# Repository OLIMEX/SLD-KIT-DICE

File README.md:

# SLD-KIT-DICE

Electronic dice soldering kit: shake it, and it spins with sound and lands on a random number.

- CH32V003J4M6 RISC-V microcontroller, 7 LEDs, shock sensor, speaker
- One CR2032 coin cell, ~6 µA in standby
- Through-hole parts only, except the SOP-8 microcontroller

Български: [README_BG.md](README_BG.md)

## Licensee
* Hardware is released under CERN Open Hardware Licence Version 2 - Strongly Reciprocal https://spdx.org/licenses/CERN-OHL-S-2.0.html
* Software is released under MIT Licensee
* Documentation is released under CC BY-SA 4.0 https://creativecommons.org/licenses/by-sa/4.0/

## Repository

| Folder | Content |
|---|---|
| [DOCUMENTS](DOCUMENTS) | [Soldering guide](DOCUMENTS/SLD-KIT-DICE_Soldering_Guide.pdf) and 2-page quick guide in [English](DOCUMENTS/SLD-KIT-DICE_Quick_Soldering_Guide.pdf) and [Bulgarian](DOCUMENTS/SLD-KIT-DICE_Quick_Soldering_Guide_BG.pdf) (PDF, and ODT to edit) |
| [HARDWARE/SLD-KIT-DICE_Rev_A](HARDWARE/SLD-KIT-DICE_Rev_A) | KiCad project, [schematic (PDF)](HARDWARE/SLD-KIT-DICE_Rev_A/SLD-KIT-DICE_Rev_A.pdf), [BOM](HARDWARE/SLD-KIT-DICE_Rev_A/SLD-KIT-DICE_Rev_A_BOM.csv), Gerber files, 3D models |
| [SOFTWARE/SLD-KIT-DICE_FW](SOFTWARE/SLD-KIT-DICE_FW) | Firmware source (ch32fun + PlatformIO) |
| [SOFTWARE/SLD-KIT-DICE_FW/firmware](SOFTWARE/SLD-KIT-DICE_FW/firmware) | Ready-to-flash images |

## Programming

Connect a WCH-LinkE to the PGM/DBG header: pin 1 = SWIO, pin 2 = GND. The header has no VCC, so the battery must be in. The chip accepts the programmer only in the first 3 s after the battery is put in: start the command, then put the battery in.

```bash
cd SOFTWARE/SLD-KIT-DICE_FW
until minichlink -w firmware/dice.bin 0x08000000 -b; do sleep 0.2; done
```

With PlatformIO (builds and flashes):

```bash
cd SOFTWARE/SLD-KIT-DICE_FW
until pio run -t upload; do sleep 0.2; done
```

How the firmware works, how to build it and how to debug it: [SOFTWARE/SLD-KIT-DICE_FW/README.md](SOFTWARE/SLD-KIT-DICE_FW/README.md).

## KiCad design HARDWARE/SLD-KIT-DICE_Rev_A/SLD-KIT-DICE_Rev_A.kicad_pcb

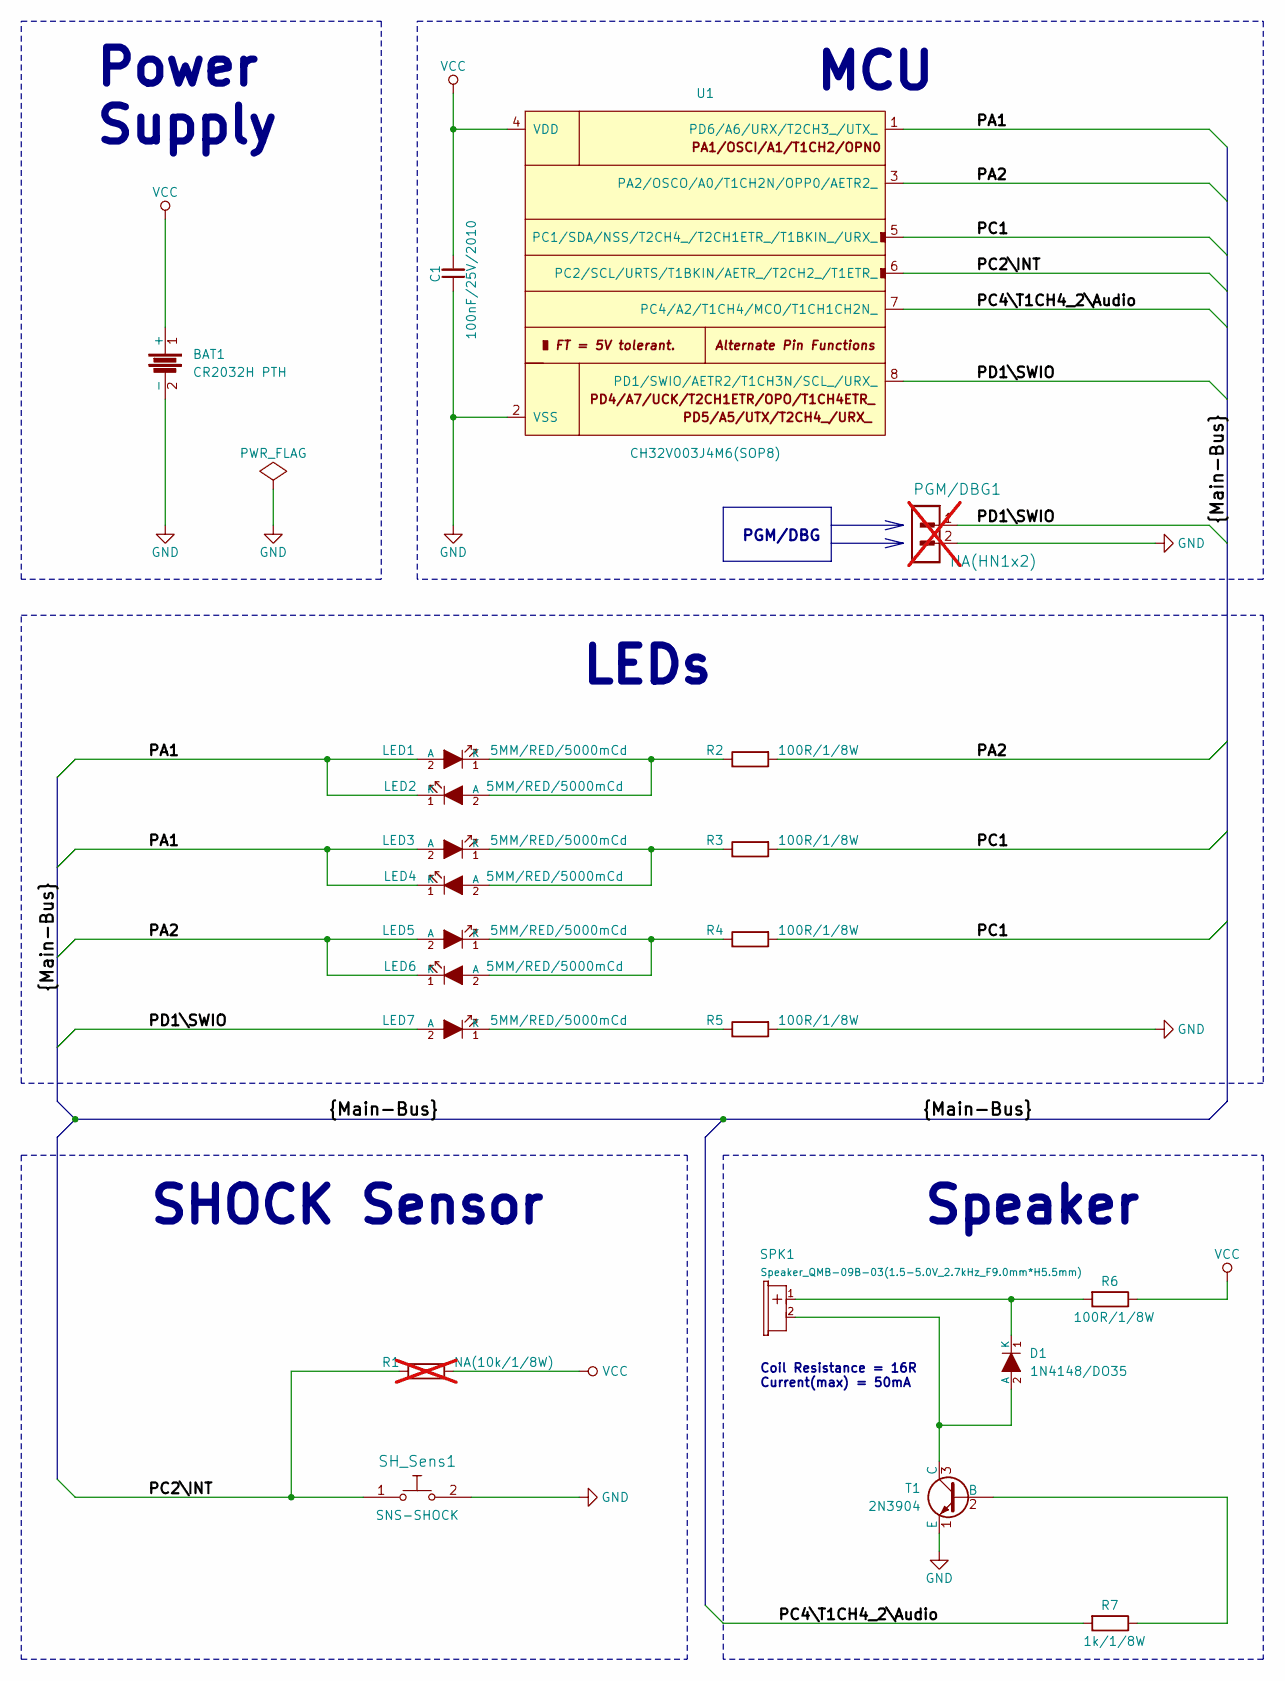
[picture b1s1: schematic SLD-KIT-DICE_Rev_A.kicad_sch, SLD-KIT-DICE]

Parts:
BAT1: CR2032H PTH; CR2032H_PTH
C1: 100nF/25V/2010; C2010
D1: 1N4148/DO35; DO35_1K_2A
LED1, LED2, LED3, LED4, LED5, LED6, LED7: 5MM/RED/5000mCd; LED-5mm-PTH-KA
PGM/DBG1: NA(HN1x2); HN1x2; not fitted
R1: NA(10k/1/8W); R_0.125W_PTH; not fitted
R2, R3, R4, R5, R6: 100R/1/8W; R_0.125W_PTH
R7: 1k/1/8W; R_0.125W_PTH
SH_Sens1: SNS-SHOCK; SNS-SHOCK-SENSOR
SPK1: Speaker_QMB-09B-03(1.5-5.0V_2.7kHz_F9.0mm*H5.5mm); Speaker_QMB-09B-03_1-Plus_2-Minus
T1: 2N3904; TO-92_PTH
U1: CH32V003J4M6(SOP8); SOIC-8_150mil

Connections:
/PA1: LED1.2 (A), LED2.1 (K), LED3.2 (A), LED4.1 (K), U1.1 (PD6/A6/URX/T2CH3_/UTX_)
/PA2: LED5.2 (A), LED6.1 (K), R2.2, U1.3 (PA2/OSCO/A0/T1CH2N/OPP0/AETR2_)
/PC1: R3.2, R4.2, U1.5 (PC1/SDA/NSS/T2CH4_/T2CH1ETR_/T1BKIN_/UR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)
/PC2\INT: R1.1, SH_Sens1.1, U1.6 (PC2/SCL/URTS/T1BKIN/AETR_/T2CH2_/T1ETR_)
/PC4\T1CH4_2\Audio: R7.2, U1.7 (PC4/A2/T1CH4/MCO/T1CH1CH2N_)
/PD1\SWIO: LED7.2 (A), PGM/DBG1.1, U1.8 (PD1/SWIO/AETR2/T1CH3N/SCL_/URX_)
GND: BAT1.2 (-), C1.1, PGM/DBG1.2, R5.2, SH_Sens1.2, T1.1 (E), U1.2 (VSS)
unnamed: D1.2 (A), SPK1.2 (MINUS), T1.3 (C)
unnamed: D1.1 (K), R6.2, SPK1.1 (PLUS)
unnamed: LED1.1 (K), LED2.2 (A), R2.1
unnamed: LED3.1 (K), LED4.2 (A), R3.1
unnamed: LED5.1 (K), LED6.2 (A), R4.1
unnamed: LED7.1 (K), R5.1
unnamed: R7.1, T1.2 (B)
VCC: BAT1.1 (+), C1.2, R1.2, R6.1, U1.4 (VDD)

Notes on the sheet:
Power Supply
LEDs
MCU
Speaker
Coil Resistance = 16R Current(max) = 50mA
PGM/DBG
SHOCK Sensor

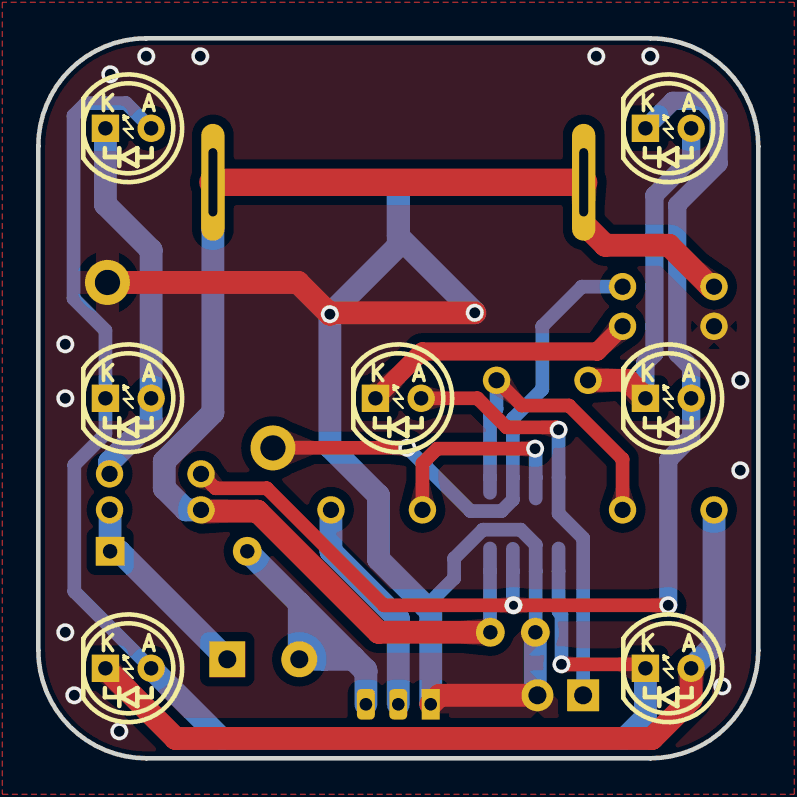
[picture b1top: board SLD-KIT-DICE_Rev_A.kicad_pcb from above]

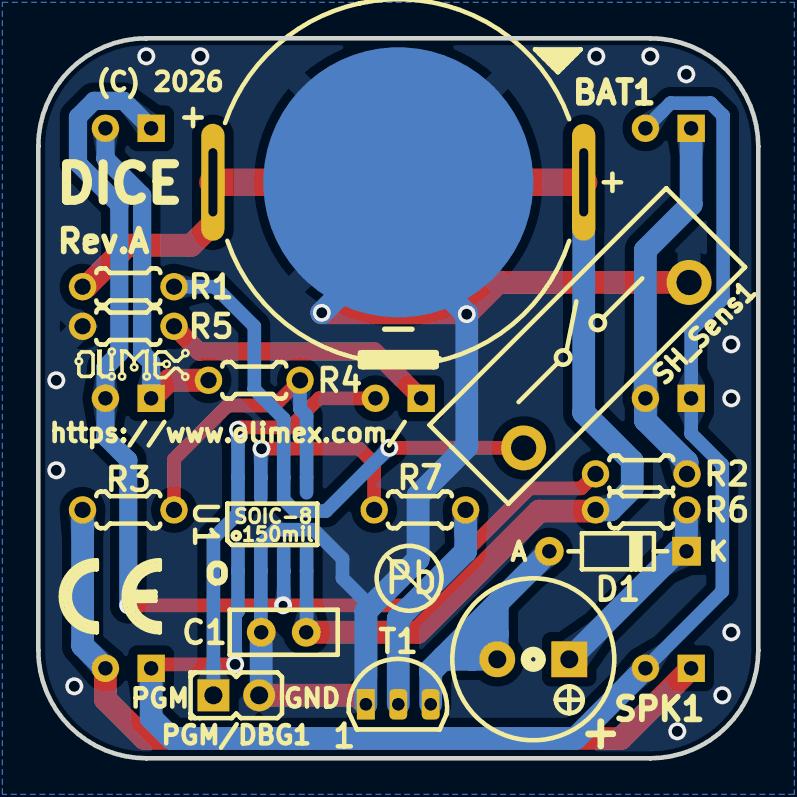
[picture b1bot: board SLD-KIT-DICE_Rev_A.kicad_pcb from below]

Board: 2 copper layers, 40.0 x 40.0 mm, 25 parts (18 on the bottom side), 15 nets.

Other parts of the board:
Logo_OLIMEX_SMALL_TB: Logo_OLIMEX_SMALL_TB
Sign_CE: CE_Sign
Sign_PB-Free: Sign_PB-Free

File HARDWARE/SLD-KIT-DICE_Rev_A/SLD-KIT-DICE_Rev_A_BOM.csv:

Quantity,Value,Footprint,Reference
1,CR2032H PTH,CR2032H_PTH,BAT1
1,100nF/25V/2010,C2010,C1
1,1N4148/DO35,DO35_1K_2A,D1
7,LED/PTH/5MM/RED,LED-5mm-PTH-KA,"LED1, LED2, LED3, LED4, LED5, LED6, LED7"
1,HN1x2,HN1x2,PGM/DBG1
5,100R/1/8W,R_0.125W_PTH,"R2, R3, R4, R5, R6"
1,1k/1/8W,R_0.125W_PTH,R7
1,SNS-SHOCK,SNS-SHOCK-SENSOR,SH_Sens1
1,Speaker_QMB-09B-03(1.5-5.0V_2.7kHz_F9.0mm*H5.5mm),Speaker_QMB-09B-03_1-Plus_2-Minus,SPK1
1,2N3904,TO-92_PTH,T1
1,CH32V003J4M6(SOP8),SOIC-8_150mil,U1

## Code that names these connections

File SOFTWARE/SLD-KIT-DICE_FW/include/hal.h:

// SPDX-License-Identifier: MIT
// Copyright (c) 2026 OLIMEX LTD BULGARIA
//
// SLD-KIT-DICE Rev.A - hardware layer (HAL)
//
// Everything that touches the chip's registers lives in hal.c. The programs
// (src/dice, src/blink) only use the functions and variables declared here.
//
// Pins (CH32V003J4M6, SOP-8). Some SOP-8 pins are bonded to two pads inside
// the package; the second pad is kept as a floating input so it never fights
// the first one.
//   pin 1  PA1 (+PD6 bonded)    charlieplex line
//   pin 2  VSS
//   pin 3  PA2                  charlieplex line
//   pin 4  VDD                  CR2032, 2.7..3.0 V
//   pin 5  PC1                  charlieplex line
//   pin 6  PC2                  shock sensor to GND, internal pull-up
//   pin 7  PC4 / TIM1_CH4       speaker via 2N3904 (high = coil on)
//   pin 8  PD1/SWIO (+PD4,PD5)  LED7 (centre) to GND via 100R, and the
//                               programming pin (see hal_release_swio)
//
// LED layout (front view):     Charlieplex (anode -> cathode):
//   LED1   .    LED6            LED1 PA1->PA2   LED2 PA2->PA1
//   LED2  LED7  LED5            LED3 PA1->PC1   LED4 PC1->PA1
//   LED3   .    LED4            LED5 PA2->PC1   LED6 PC1->PA2
//
// Charlieplexing: 3 pins drive 6 LEDs. To light LED1, PA1 goes high, PA2 low
// and PC1 is left floating (input), so current can flow only through LED1.
// Only LEDs that share the same high pin can be on at once, so the LEDs are
// shown one group at a time, fast enough (250 Hz) that the eye sees them all.

#ifndef HAL_H
#define HAL_H

#include <stdint.h>
#include "ch32fun.h"

// ---- LEDs ------------------------------------------------------------------
// hal_leds is a bit mask of these. Write it at any time; the scanner in the
// SysTick interrupt shows it from the next millisecond on.
#define LED1 (1u << 0)  // top left
#define LED2 (1u << 1)  // middle left
#define LED3 (1u << 2)  // bottom left
#define LED4 (1u << 3)  // bottom right
#define LED5 (1u << 4)  // middle right
#define LED6 (1u << 5)  // top right
#define LED7 (1u << 6)  // centre (PD1/SWIO, lit only after hal_release_swio)
#define LED_ALL 0x7Fu

#define SPK_RESONANCE_HZ 2700   // QMB-09B-03 speaker is loudest here

// ---- state shared with the interrupts --------------------------------------
extern volatile uint32_t hal_ms;          // milliseconds since start (stops in standby)
extern volatile uint8_t  hal_leds;        // LED bit mask shown by the scanner
extern volatile uint32_t hal_shock_count; // sensor closings (approximate: max 2 per ms)
extern volatile uint32_t hal_shock_ms;    // hal_ms of the last closing
extern volatile uint32_t hal_shock_events;// ms ticks that saw at least one closing
extern uint32_t hal_reset_flags;          // RCC->RSTSCKR at start (RCC_*RSTF bits)
extern uint32_t hal_boot_mcause;          // mcause at start; with no reset flags set,
                                          // non-zero = we got here through a trap

// ---- RAM kept across resets ------------------------------------------------
// The top of RAM is not touched by the start-up code (it is outside .data and
// .bss), so it keeps its contents through a reset, and also through a power
// dip short enough for the RAM cells to hold their charge. After the battery
// has been out for a while it holds random values, so everything stored here
// carries a "magic" word that marks it as valid.
//   0x20000400  crash record (24 bytes, hal_crash_t)
//   0x20000418  phase the application last reported (hal_set_phase)
//   0x2000041C  not used
//   0x20000420  free for the application (dice: statistics and resume marker)
// The stack grows down from 0x20000800. The dice uses a few hundred bytes of
// it at most, well clear of the ~0x3A0 bytes above the dice's data.

// Crash record. HardFault/NMI store it here and reset the chip, instead of
// hanging. Read it with:  minichlink -r crash.bin 0x20000400 24
typedef struct {
	uint32_t magic;     // HAL_CRASH_MAGIC when valid
	uint32_t mcause;    // 2 = illegal instruction, 1/5/7 = access faults, ...
	uint32_t mepc;      // address of the faulting instruction (see addr2line)
	uint32_t mtval;     // bad address / bad instruction
	uint32_t intsyscr;  // CSR 0x804: bit0 hardware stack, bit1 nesting
	uint32_t count;     // crashes since power-on
} hal_crash_t;

#define HAL_CRASH_ADDR  0x20000400u
#define HAL_CRASH       ((volatile hal_crash_t *)HAL_CRASH_ADDR)
#define HAL_CRASH_MAGIC 0xDEADD1CEu

extern hal_crash_t hal_last_crash;        // copy taken at start, magic = 0 if none

#define HAL_PHASE_ADDR  0x20000418u
#define HAL_PHASE       (*(volatile uint32_t *)HAL_PHASE_ADDR)
#define HAL_PHASE_MAGIC 0x50480000u
#define HAL_APP_RAM     ((volatile uint32_t *)0x20000420u)

// The application reports what it is doing, so a reset can be traced back.
static inline void hal_set_phase(uint8_t p) { HAL_PHASE = HAL_PHASE_MAGIC | p; }
extern uint32_t hal_last_phase;           // phase before the last reset, 0 = unknown

// ---- functions -------------------------------------------------------------

// Clocks, pins, timers, interrupts. Call once, right after SystemInit().
void hal_init(void);

// Turn PD1 from SWIO into a GPIO for LED7. After this the chip can be
// programmed only right after power-up (take the battery out and back in).
void hal_release_swio(void);
int  hal_swio_released(void);

// Speaker. Non-blocking: the tone stops by itself after ms (ms = 0: until
// hal_tone_off). The LEDs are dark while a tone plays, so the battery never
// has to feed both at once.
void hal_tone(uint16_t hz, uint16_t ms);
void hal_tone_off(void);
int  hal_tone_busy(void);
extern volatile uint8_t hal_tone_duty;    // PWM duty %, default 50 (lower = quieter,
                                          // less current)

// LED on-time in each 1 ms scan slot, in eighths: 8 = full, 4 = half current.
void hal_led_level(uint8_t level);

// Wait ms milliseconds in light sleep (the CPU halts until the next tick).
void hal_delay(uint32_t ms);

// Standby until the shock sensor fires (~6 uA). LEDs and sound go off, and
// hal_ms stops while asleep.
void hal_sleep_until_shock(void);

// Entropy pool fed by the sensor's edge times (24 MHz captures). Hash it
// before use; see rng_mix() in src/dice/main.c.
uint32_t hal_entropy(void);

#endif
